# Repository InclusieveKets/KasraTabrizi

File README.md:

## Session 1
[Session1](./session1)

## Session 2
[Session2](./session2)

## Session 3
[Session3](./session3)

## Session 4
[Session4](./session4)

## Session 5
[Session5](./session5)

## Session 6
[Session6](./session6)

## Session 7
[Session7](./session7)

## Session 8
[Session8](./session8)

## Session 9
[Session9](./session9)

## Session 10
[Session10](./session10)

## Session 11
[Session11](./session11)

## Session 12
[Session12](./session12)

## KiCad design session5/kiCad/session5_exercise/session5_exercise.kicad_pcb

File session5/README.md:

# SESSION 5 (01/04/2020)
## Author: Kasra Tabrizi

- Introduction to KiCad
- Learning to Draw schematics
- Learning to create PCB layouts for those schematics

### History

In the early days of electronics, components were just soldered together.

This made it very difficult to replace a component or to troubleshoot. Everything looks messy at the end.

That why they invented the PCB board where components would be mounted on a green board and connected via copper lanes.

### Prototype

Prototyping of a circuit could be done in several ways.

You can use PCB with predrilled holes

You can use a breadboard

### PCB Production methods

#### Milling

The disadvantage of milling is that you are limited to the smallest mill cutter. Mill cutters also worn out pretty fast.

#### Etching

Etching is the process where you etch away all the copper on the PCB that you dont need revealing only the copper lanes.

### Assignment

- Make a small schematic that consist of a battery holder, switch, LED and resistor.
- make the PCB layer of it

#### Process

##### Schematic

##### PCB Layout

##### 3D View

### Design files

<ul>
    <li><a href="kiCad/session5_exercise/session5_exercise.sch" download>session 5 exercise schematic</a></li>
    <li><a href="kiCad/session5_exercise/session5_exercise.kicad_pcb" download>session 5 exercise pcb</a></li>
</ul>

[Go Back](../README.md)

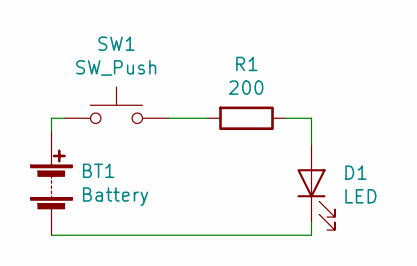
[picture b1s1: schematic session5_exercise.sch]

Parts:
BT1: Battery; BatteryHolder_Eagle_12BH611-GR
D1: LED; LED_D4.0mm
R1: 200; R_Axial_DIN0309_L9.0mm_D3.2mm_P15.24mm_Horizontal
SW1: SW_Push; SW_PUSH-12mm

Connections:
unnamed: BT1.1 (+), SW1.1
unnamed: BT1.2 (-), D1.1 (K)
unnamed: D1.2 (A), R1.1
unnamed: R1.2, SW1.2

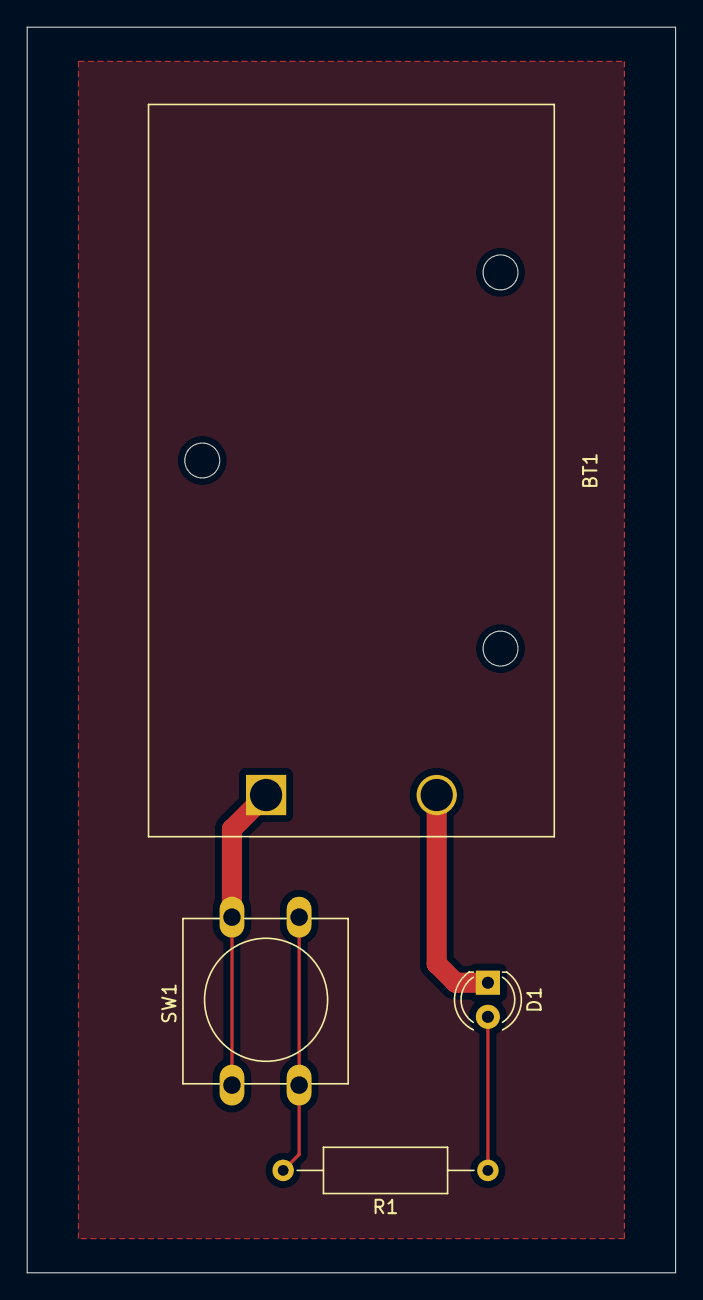
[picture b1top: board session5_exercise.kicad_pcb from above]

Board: 2 copper layers, 48.3 x 92.7 mm, 4 parts (0 on the bottom side), 4 nets.

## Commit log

2020-03-04 Set theme jekyll-theme-minimal
2020-03-04 Overview of session 1
2020-03-04 Update README.md
    added h1 and h3 header
2020-03-04 added the assets and images folder together with the profile image
2020-03-04 added profile image
2020-03-04 update README.md
    add profile, hobbies, code example and social media sections
2020-03-04 update the link text of facebook link
2020-03-04 Set theme jekyll-theme-leap-day
2020-03-11 added readme to session 2
2020-03-11 added readme files to all the folders
2020-03-11 added the links to all the sessions
2020-03-11 added inkscape file and added comments to readme
2020-03-12 update session2 readme
2020-03-14 added report of smartphone stand
2020-03-14 added placeholdern images
2020-03-14 added header for the process section
2020-03-14 deleted some whitespaces
2020-03-14 added images
2020-03-18 added all the images for session 2
2020-03-18 added first image of the phone stand
2020-03-18 changed first picture. github rotates picture for some strange reason
2020-03-18 changed width to 200 of the first image
2020-03-18 changed width to 100
2020-03-18 deleted the width attribute, it doesnt work
2020-03-18 changed width of images with paint
2020-03-18 change width again
2020-03-18 changed the markdown notation into an html img tag for adding the images and to adjust the width
2020-03-18 deleted comment
2020-03-18 added second image and corrected some typos
2020-03-18 added third images and correct typos for the description of the second version
2020-03-18 added image
2020-03-18 added 4th image with the negraved symbols
2020-03-18 cropped and added some text for the shields image
2020-03-18 corrected some typos and added the project shield image
2020-03-18 gave some images a width of 400
2020-03-18 added the optimal image positioning in inkscape
2020-03-18 changed name of the optimal image positioning images
2020-03-18 changed the extentions to png instead of jpg
2020-03-18 deleted the width, changed the alt message
2020-03-18 changed text a bit on how to work with the lasercutter
2020-03-18 added p tag to center the images
2020-03-18 change on text
2020-03-18 changed the width of the project shield image
2020-03-18 made some changes in the text. numbering headers , etc
2020-03-18 added date to session 3 readme file + 3d introduction descriptionf
2020-03-18 added text to sessio 3
2020-03-18 changes to text
2020-03-24 removed FabZeroAlgemeen and Welcome to your new FabZero sections
2020-03-24 added things to learn in section 1
2020-03-24 added go back button to go back to the landing page
2020-03-24 making the go back button work
2020-03-24 now it should work
2020-03-24 now it should work for real! :)
2020-03-24 added go back button to section 3
2020-03-24 added go back button to section 2
2020-03-24 added link in the YHT rules section for printen different 3d models for testing
2020-03-24 added project description plus image
2020-03-24 added the images and described the steps for the process of the assignment
2020-03-24 changed width of image of step 3 to 400
2020-03-24 extension of last 2 images are jpg instead of png
2020-03-24 typo in image name
2020-03-24 extension of last to images are jpeg instead of jpg :)
2020-03-24 typo in image name. needs to underscore instead of dash
2020-03-24 changed the width of first and last 2 images to 400
2020-03-25 added link to the inkscape files for sessions 2
2020-03-25 link to the shield.svg
2020-03-25 typo
2020-03-25 added a a tag with the download attribute instead of a markdown link
2020-03-25 give name to a tag
2020-03-25 added the download links for session 2
2020-03-25 added li tag
2020-03-25 added download links for session 3
2020-03-25 session 4: introduction to Electronics
2020-03-26 session 4 notes
2020-03-26 changed line 5 and 6
2020-03-26 deleted whitespace
2020-04-01 busy with assignment session 4 and added intro to session 5
2020-04-18 added screenshot of led matrix display for calculations
2020-04-18 changed width of image
2020-04-18 connected the 5V en GND from arduino to power supply in schematic
2020-04-18 added amazon link
2020-04-18 added basic calculation
2020-04-18 wefwe
2020-04-18 put the calculations in quotes
2020-04-21 added intro to session 5
2020-04-21 aded two pictures and description for the history section
2020-04-24 added intro and back button
2020-04-24 changed image
2020-04-24 added real circuit
2020-04-24 fdfsd
2020-04-24 change orientation
2020-04-24 changed orientation
2020-04-24 added sourcode
2020-04-30 added assignment to session 7
2020-05-06 session 8
2020-05-12 added end project questions
2020-05-12 got rid of a hypen
2020-05-12 updated first answer
